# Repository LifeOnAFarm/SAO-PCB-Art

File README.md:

# SAO PCB Art 
Created in the lead up to DefCon 26 #BadgeLife

## Getting Started

Welcome to a collection of my PCB Shitty Add-On (SAO) files.

Here you will find svg images, schematics, gerbers and all the Kicad files you need to edit and make your own SAO PCB. I recommend @MrTwinkleTwink's video on how to convert svg images to Kicad files using Inkscape if you want to make any board chances (https://youtu.be/61NFK9KW).

# Chain Chomp

## Components You Will Need:

- 1 x 0.1" 2x2 Female Headers

- 5 x 1206 LEDS (Solder these with the top of the LED facing towards the PCB board)

- 1 x 2512 51 ohm Resistor

# Shy Guy

## Components You Will Need:

- 1 x 0.1" 2x2 Female Headers

- 2 x 1206 LEDS (Solder these with the top of the LED facing towards the PCB board)

- 1 x 2512 51 ohm Resistor

## Authors

- Seamus de Cleir (@PotatoNightmare)

## License

This project is licensed under the MIT License. 

All I ask is that you leave my Twitter handle on the back of the board, thanks. - see the LICENSE.md file for more details

## Acknowledgments

@MrTwinkleTwink for the great tutorial on SAO's 

## Donations

A button to buy me a cup of coffee if you see fit

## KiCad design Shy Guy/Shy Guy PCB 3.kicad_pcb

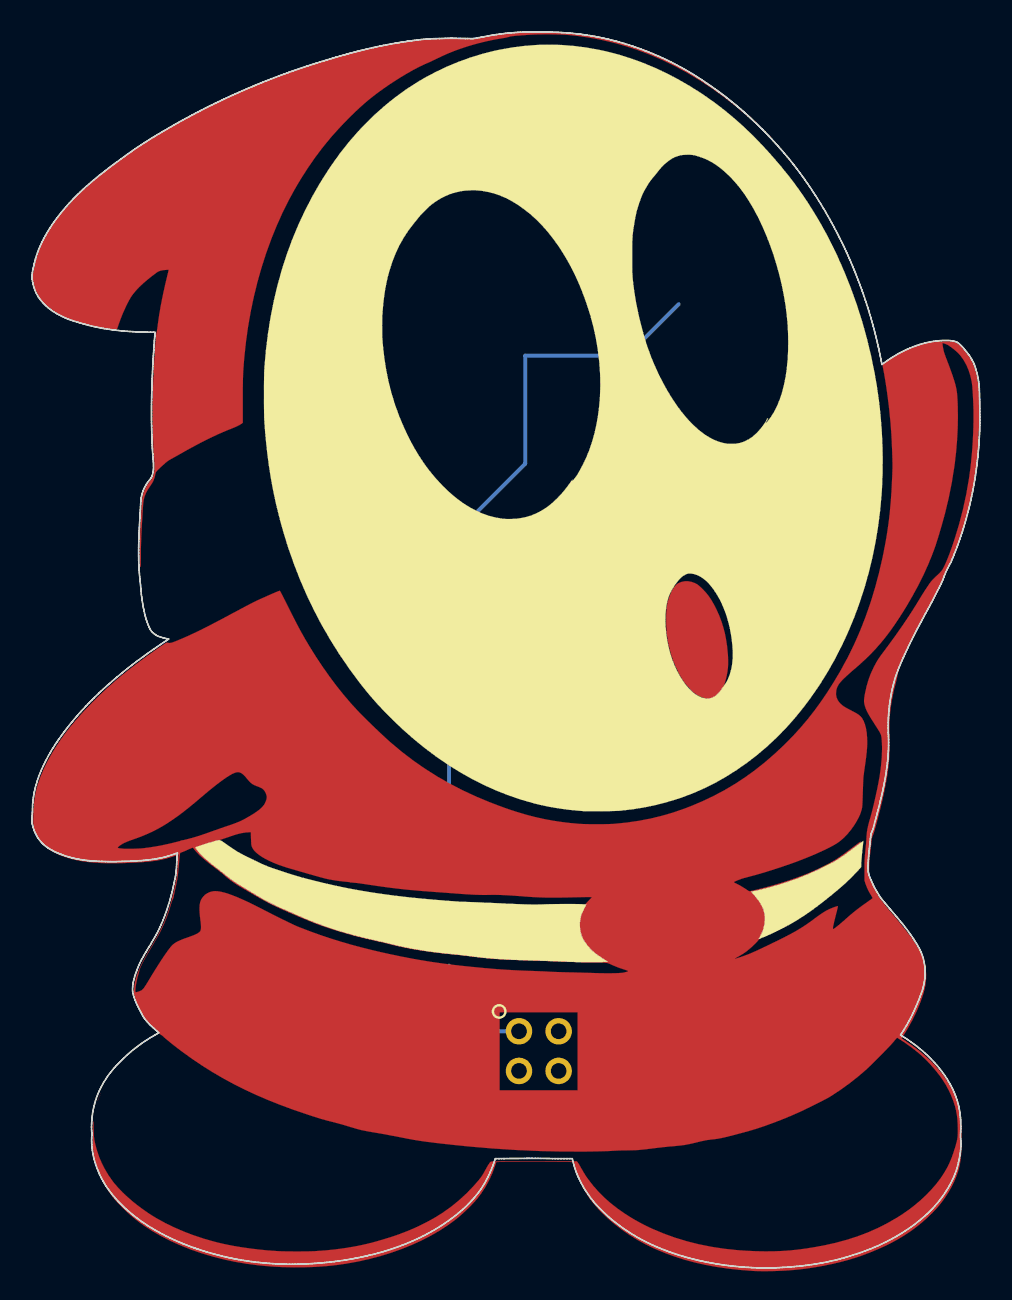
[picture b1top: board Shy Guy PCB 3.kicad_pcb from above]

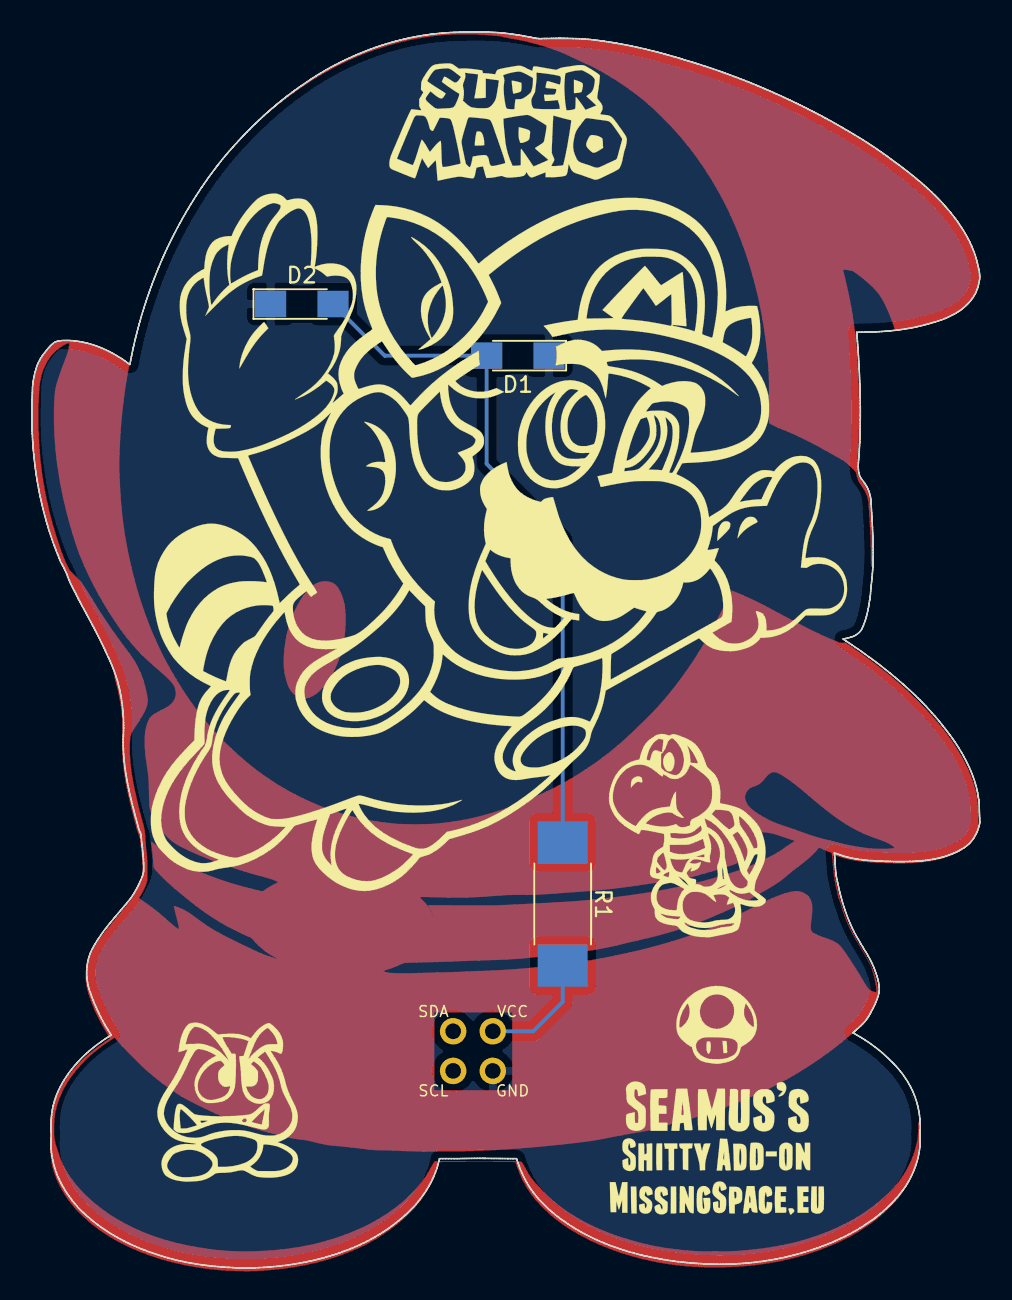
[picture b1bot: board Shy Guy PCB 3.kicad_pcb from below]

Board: 2 copper layers, 60.7 x 79.2 mm, 4 parts (3 on the bottom side), 3 nets.

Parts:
D1, D2: LED; LED_1206_HandSoldering
R1: R51; R_2512_HandSoldering
X1: Badgelife_shitty_connector; Badgelife-Shitty-2x2

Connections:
unnamed: D1.1, D2.1, X1.2
unnamed: D1.2, D2.2, R1.1
unnamed: R1.2, X1.1

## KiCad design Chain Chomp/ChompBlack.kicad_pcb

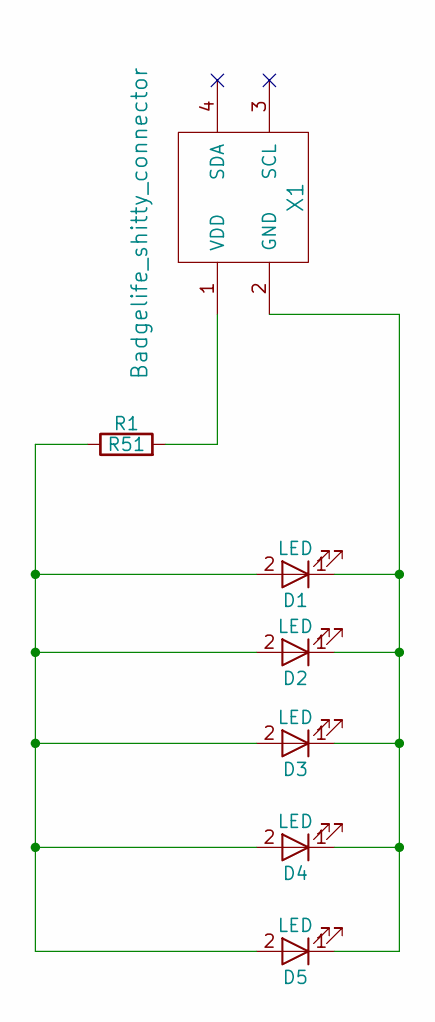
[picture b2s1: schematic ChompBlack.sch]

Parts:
D1, D2, D3, D4, D5: LED; LED_1206_HandSoldering
R1: R51; R_2512_HandSoldering
X1: Badgelife_shitty_connector; Badgelife-Shitty-2x2

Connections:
unnamed: D1.1 (K), D2.1 (K), D3.1 (K), D4.1 (K), D5.1 (K), X1.2 (GND)
unnamed: D1.2 (A), D2.2 (A), D3.2 (A), D4.2 (A), D5.2 (A), R1.1
unnamed: R1.2, X1.1 (VDD)

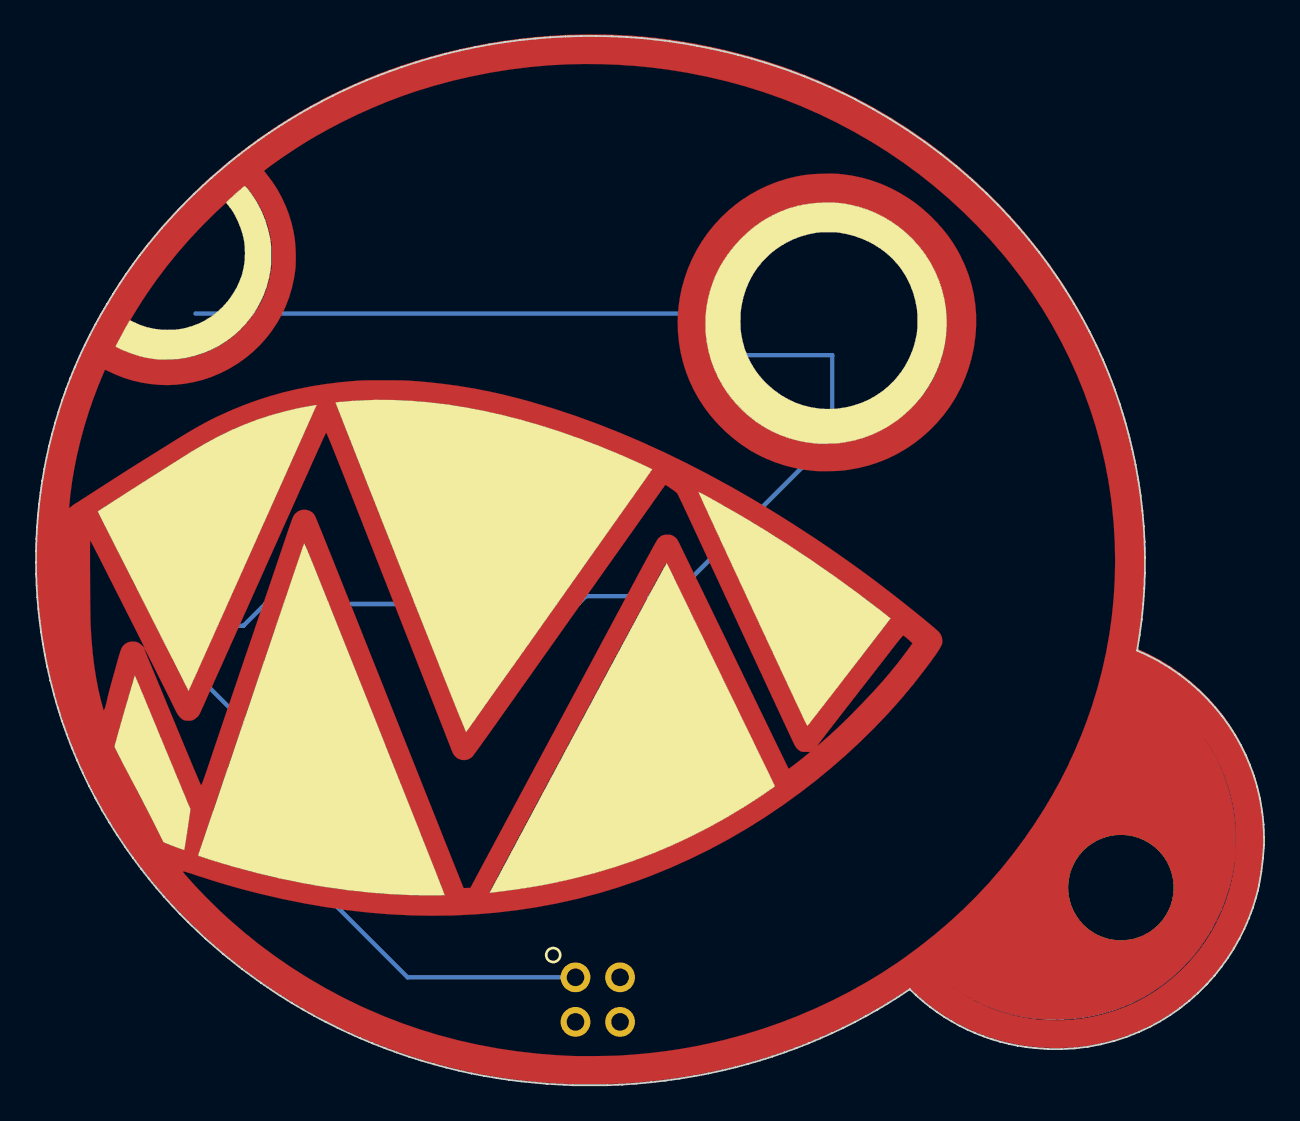
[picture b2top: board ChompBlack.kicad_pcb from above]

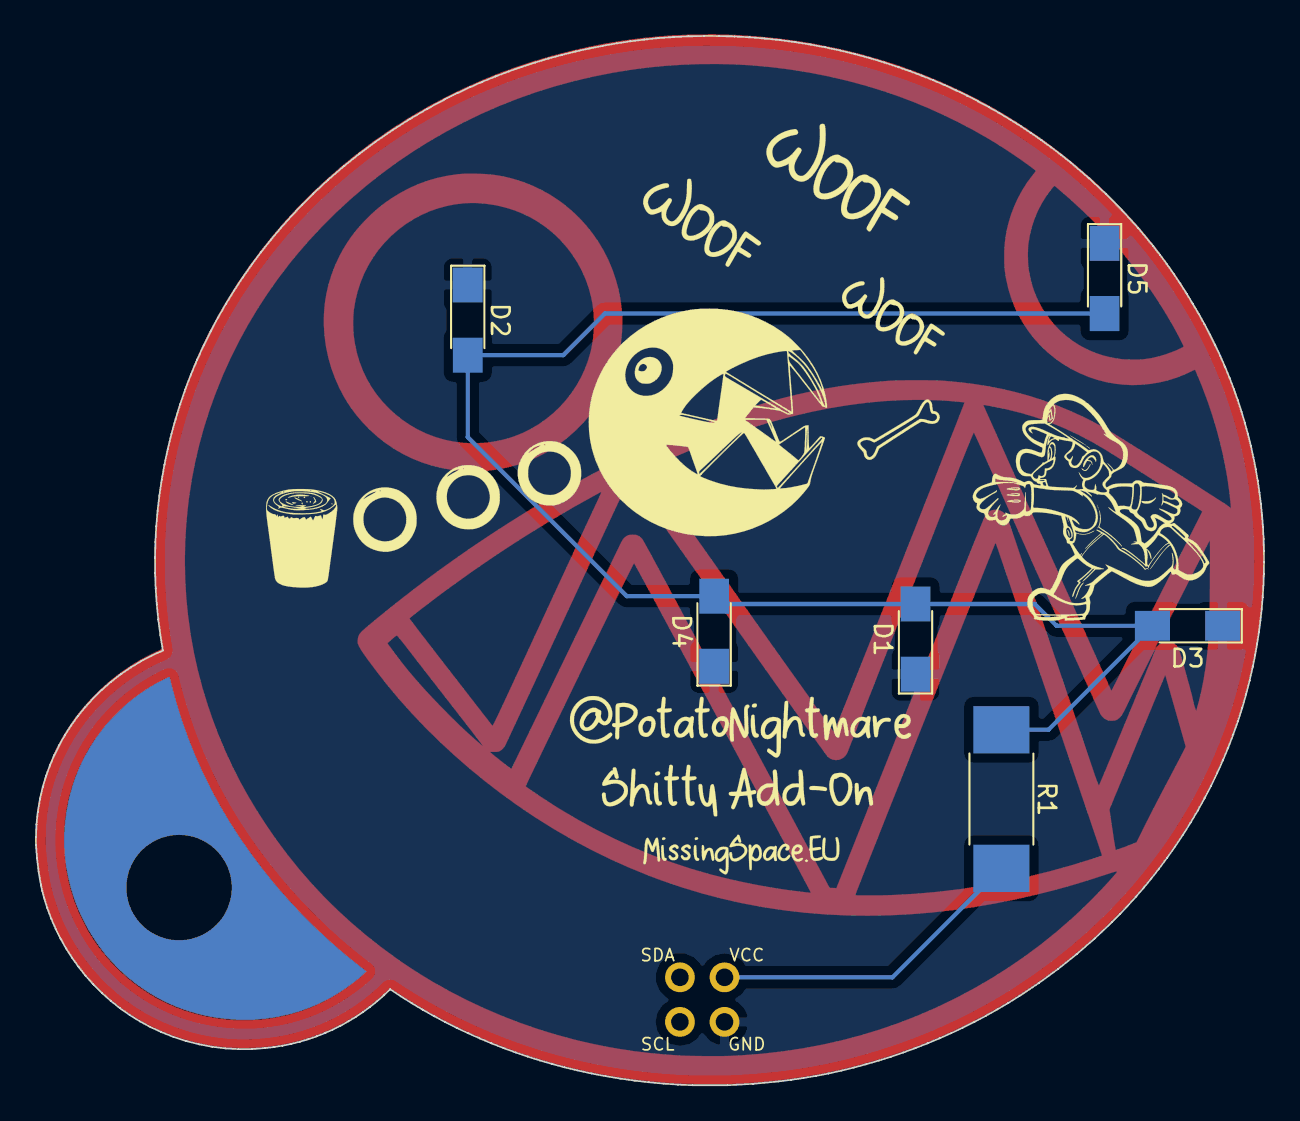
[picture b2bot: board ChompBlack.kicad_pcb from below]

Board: 2 copper layers, 70.0 x 59.8 mm, 7 parts (6 on the bottom side), 3 nets.

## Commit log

2018-07-20 Change
